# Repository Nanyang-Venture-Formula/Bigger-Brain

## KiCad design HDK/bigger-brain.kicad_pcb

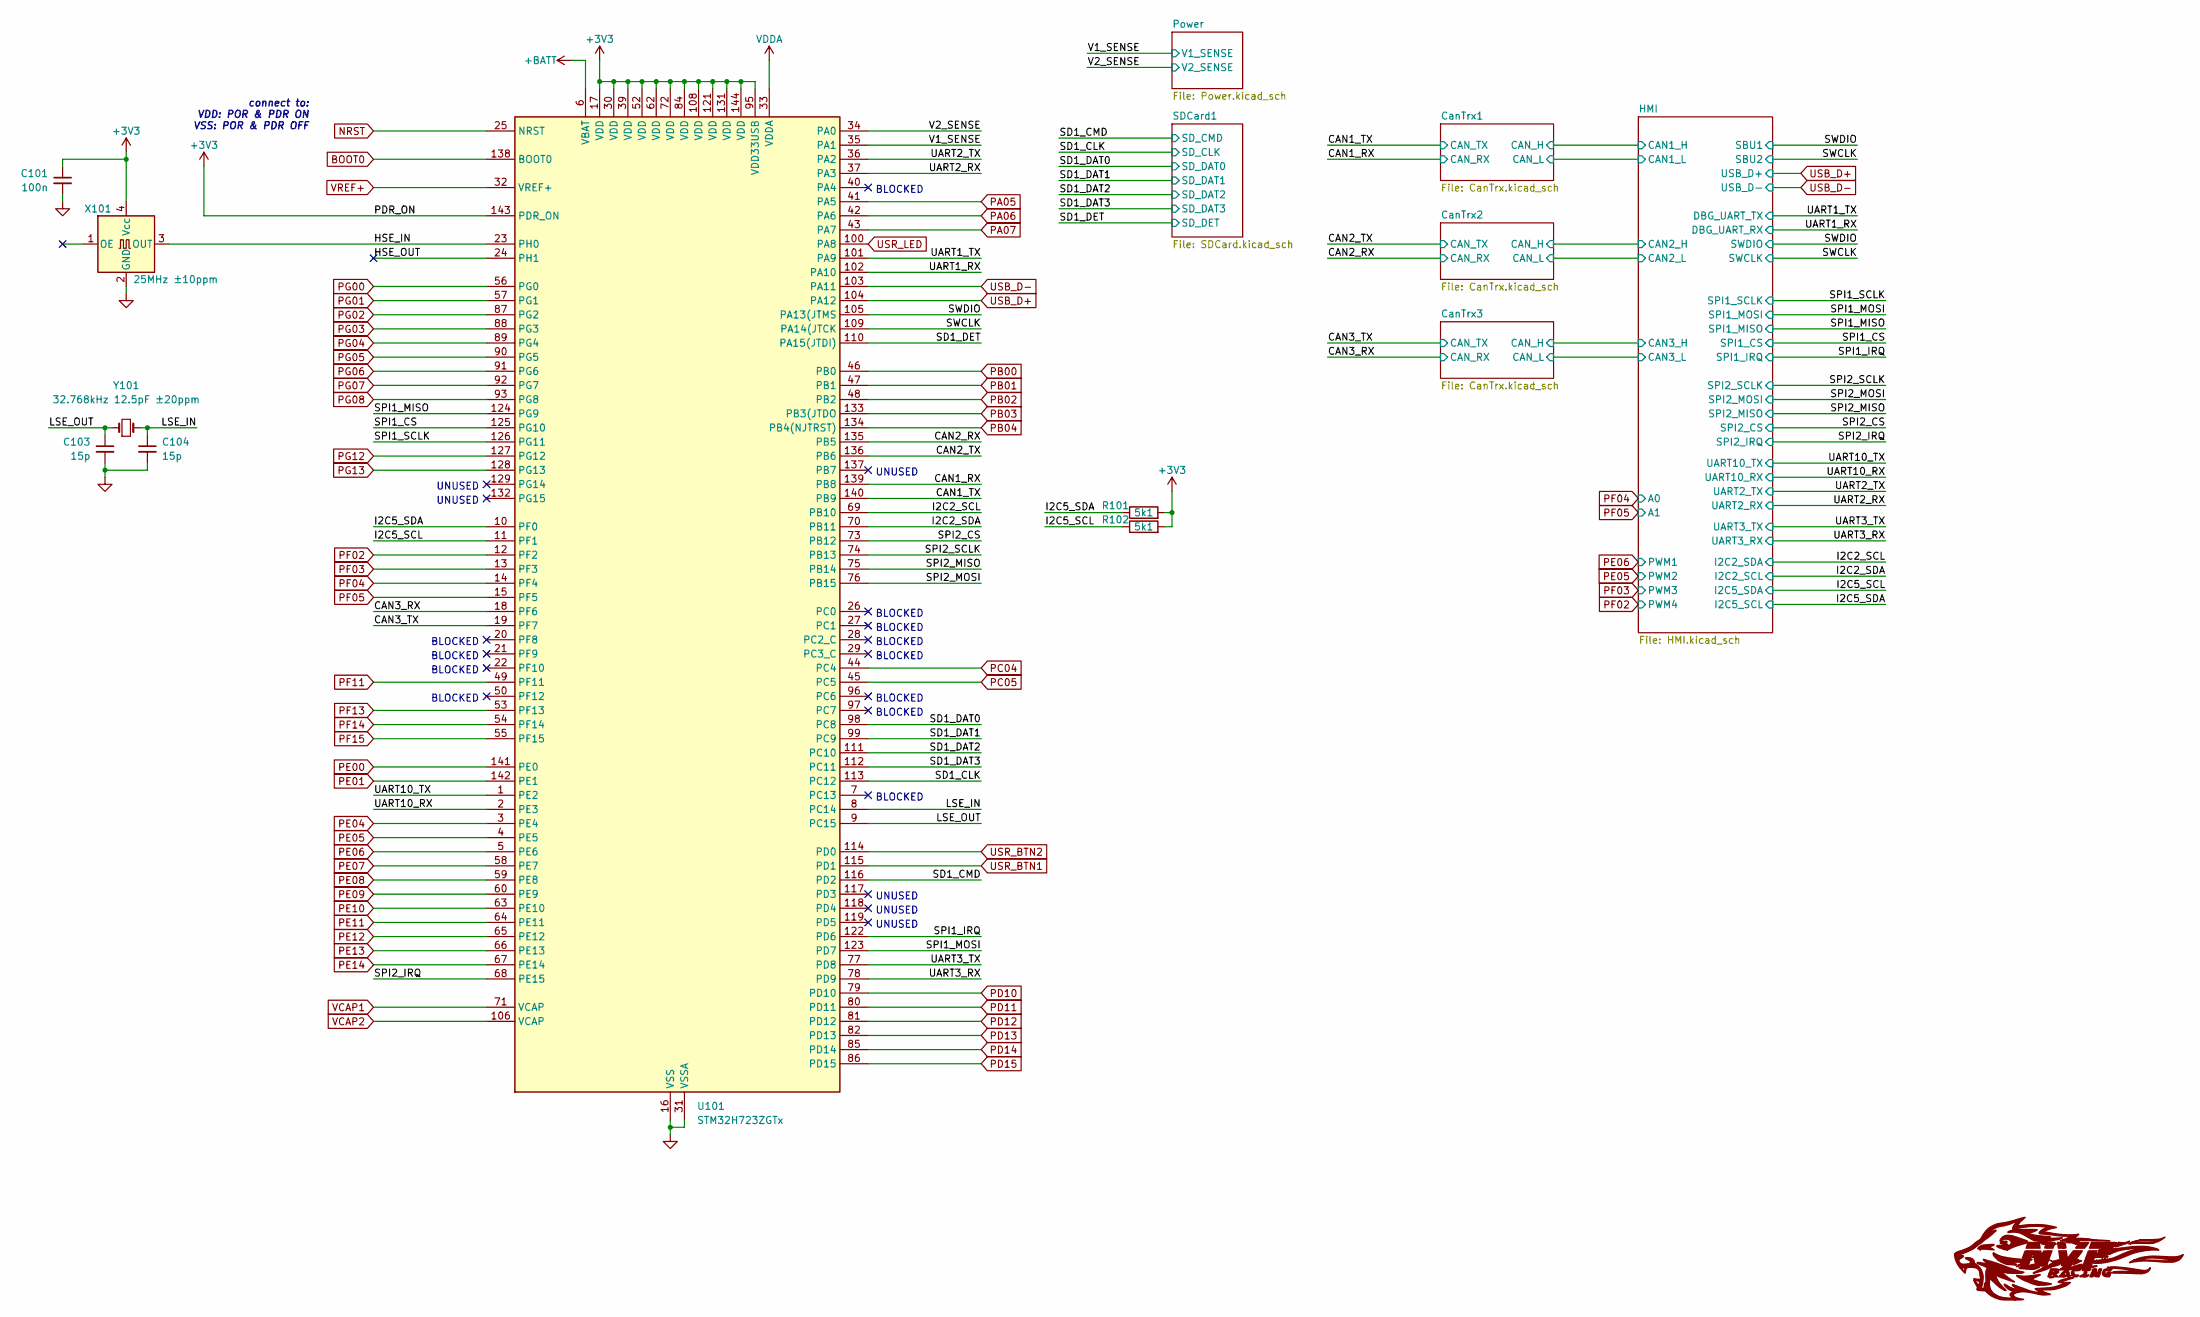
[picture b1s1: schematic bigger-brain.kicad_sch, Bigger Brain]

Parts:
C101: 100n; C_0603_1608Metric; LCSC C14663
C103, C104: 15p; C_0603_1608Metric; LCSC C1644
R101, R102: 5k1; R_0603_1608Metric; LCSC C23186
U101: STM32H723ZGTx; LQFP-144_20x20mm_P0.5mm; LCSC C730146
X101: 25MHz ±10ppm; Crystal_SMD_3225-4Pin_3.2x2.5mm; LCSC C669088
Y101: 32.768kHz 12.5pF ±20ppm; Crystal_SMD_3215-2Pin_3.2x1.5mm; LCSC C32346

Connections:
+BATT: U101.6 (VBAT); also elsewhere on the board
/CAN1_RX: U101.139 (PB8); also elsewhere on the board
/CAN1_TX: U101.140 (PB9); also elsewhere on the board
/CAN2_RX: U101.135 (PB5); also elsewhere on the board
/CAN2_TX: U101.136 (PB6); also elsewhere on the board
/CAN3_RX: U101.18 (PF6); also elsewhere on the board
/CAN3_TX: U101.19 (PF7); also elsewhere on the board
/HSE_IN: U101.23 (PH0), X101.3 (OUT)
/HSE_OUT: U101.24 (PH1)
/I2C2_SCL: U101.69 (PB10); also elsewhere on the board
/I2C2_SDA: U101.70 (PB11); also elsewhere on the board
/I2C5_SCL: R102.1, U101.11 (PF1); also elsewhere on the board
/I2C5_SDA: R101.1, U101.10 (PF0); also elsewhere on the board
/LSE_IN: C104.1, U101.8 (PC14), Y101.2
/LSE_OUT: C103.1, U101.9 (PC15), Y101.1
/SD1_CLK: U101.113 (PC12); also elsewhere on the board
/SD1_CMD: U101.116 (PD2); also elsewhere on the board
/SD1_DAT0: U101.98 (PC8); also elsewhere on the board
/SD1_DAT1: U101.99 (PC9); also elsewhere on the board
/SD1_DAT2: U101.111 (PC10); also elsewhere on the board
/SD1_DAT3: U101.112 (PC11); also elsewhere on the board
/SD1_DET: U101.110 (PA15(JTDI)); also elsewhere on the board
/SPI1_CS: U101.125 (PG10); also elsewhere on the board
/SPI1_IRQ: U101.122 (PD6); also elsewhere on the board
/SPI1_MISO: U101.124 (PG9); also elsewhere on the board
/SPI1_MOSI: U101.123 (PD7); also elsewhere on the board
/SPI1_SCLK: U101.126 (PG11); also elsewhere on the board
/SPI2_CS: U101.73 (PB12); also elsewhere on the board
/SPI2_IRQ: U101.68 (PE15); also elsewhere on the board
/SPI2_MISO: U101.75 (PB14); also elsewhere on the board
/SPI2_MOSI: U101.76 (PB15); also elsewhere on the board
/SPI2_SCLK: U101.74 (PB13); also elsewhere on the board
/SWCLK: U101.109 (PA14(JTCK); also elsewhere on the board
/SWDIO: U101.105 (PA13(JTMS); also elsewhere on the board
/UART1_RX: U101.102 (PA10); also elsewhere on the board
/UART1_TX: U101.101 (PA9); also elsewhere on the board
/UART2_RX: U101.37 (PA3); also elsewhere on the board
/UART2_TX: U101.36 (PA2); also elsewhere on the board
/UART3_RX: U101.78 (PD9); also elsewhere on the board
/UART3_TX: U101.77 (PD8); also elsewhere on the board
/UART10_RX: U101.2 (PE3); also elsewhere on the board
/UART10_TX: U101.1 (PE2); also elsewhere on the board
/V1_SENSE: U101.35 (PA1); also elsewhere on the board
/V2_SENSE: U101.34 (PA0); also elsewhere on the board
BOOT0: U101.138 (BOOT0); also elsewhere on the board
GND: C101.2, C103.2, C104.2, U101.16 (VSS), U101.31 (VSSA), U101.38 (VSS), U101.51 (VSS), U101.61 (VSS), U101.83 (VSS), U101.94 (VSS), U101.107 (VSS), U101.120 (VSS), U101.130 (VSS), X101.2 (GND); also elsewhere on the board
MCU-3.3V: C101.1, R101.2, R102.2, U101.17 (VDD), U101.30 (VDD), U101.39 (VDD), U101.52 (VDD), U101.62 (VDD), U101.72 (VDD), U101.84 (VDD), U101.95 (VDD33USB), U101.108 (VDD), U101.121 (VDD), U101.131 (VDD), U101.143 (PDR_ON), U101.144 (VDD), X101.4 (Vcc); also elsewhere on the board
NRST: U101.25 (NRST); also elsewhere on the board
PA05: U101.41 (PA5); also elsewhere on the board
PA06: U101.42 (PA6); also elsewhere on the board
PA07: U101.43 (PA7); also elsewhere on the board
PB00: U101.46 (PB0); also elsewhere on the board
PB01: U101.47 (PB1); also elsewhere on the board
PB02: U101.48 (PB2); also elsewhere on the board
PB03: U101.133 (PB3(JTDO); also elsewhere on the board
PB04: U101.134 (PB4(NJTRST)); also elsewhere on the board
PC04: U101.44 (PC4); also elsewhere on the board
PC05: U101.45 (PC5); also elsewhere on the board
PD10: U101.79 (PD10); also elsewhere on the board
PD11: U101.80 (PD11); also elsewhere on the board
PD12: U101.81 (PD12); also elsewhere on the board
PD13: U101.82 (PD13); also elsewhere on the board
PD14: U101.85 (PD14); also elsewhere on the board
PD15: U101.86 (PD15); also elsewhere on the board
PE00: U101.141 (PE0); also elsewhere on the board
PE01: U101.142 (PE1); also elsewhere on the board
PE04: U101.3 (PE4)
PE05: U101.4 (PE5); also elsewhere on the board
PE06: U101.5 (PE6); also elsewhere on the board
PE07: U101.58 (PE7); also elsewhere on the board
PE08: U101.59 (PE8); also elsewhere on the board
PE09: U101.60 (PE9); also elsewhere on the board
PE10: U101.63 (PE10); also elsewhere on the board
PE11: U101.64 (PE11); also elsewhere on the board
PE12: U101.65 (PE12); also elsewhere on the board
PE13: U101.66 (PE13); also elsewhere on the board
PE14: U101.67 (PE14); also elsewhere on the board
PF02: U101.12 (PF2); also elsewhere on the board
PF03: U101.13 (PF3); also elsewhere on the board
PF04: U101.14 (PF4); also elsewhere on the board
PF05: U101.15 (PF5); also elsewhere on the board
PF11: U101.49 (PF11); also elsewhere on the board
PF13: U101.53 (PF13); also elsewhere on the board
PF14: U101.54 (PF14); also elsewhere on the board
PF15: U101.55 (PF15); also elsewhere on the board
PG00: U101.56 (PG0); also elsewhere on the board
PG01: U101.57 (PG1); also elsewhere on the board
PG02: U101.87 (PG2); also elsewhere on the board
PG03: U101.88 (PG3); also elsewhere on the board
PG04: U101.89 (PG4); also elsewhere on the board
PG05: U101.90 (PG5); also elsewhere on the board
PG06: U101.91 (PG6); also elsewhere on the board
PG07: U101.92 (PG7); also elsewhere on the board
PG08: U101.93 (PG8); also elsewhere on the board
PG12: U101.127 (PG12); also elsewhere on the board
PG13: U101.128 (PG13); also elsewhere on the board
USB_D+: U101.104 (PA12); also elsewhere on the board
USB_D-: U101.103 (PA11); also elsewhere on the board
USR_BTN1: U101.115 (PD1); also elsewhere on the board
USR_BTN2: U101.114 (PD0); also elsewhere on the board
USR_LED: U101.100 (PA8); also elsewhere on the board
VCAP1: U101.71 (VCAP); also elsewhere on the board
VCAP2: U101.106 (VCAP); also elsewhere on the board
VDDA: U101.33 (VDDA); also elsewhere on the board
VREF+: U101.32 (VREF+); also elsewhere on the board

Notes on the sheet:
UNUSED
BLOCKED
connect to: VDD: POR & PDR ON VSS: POR & PDR OFF

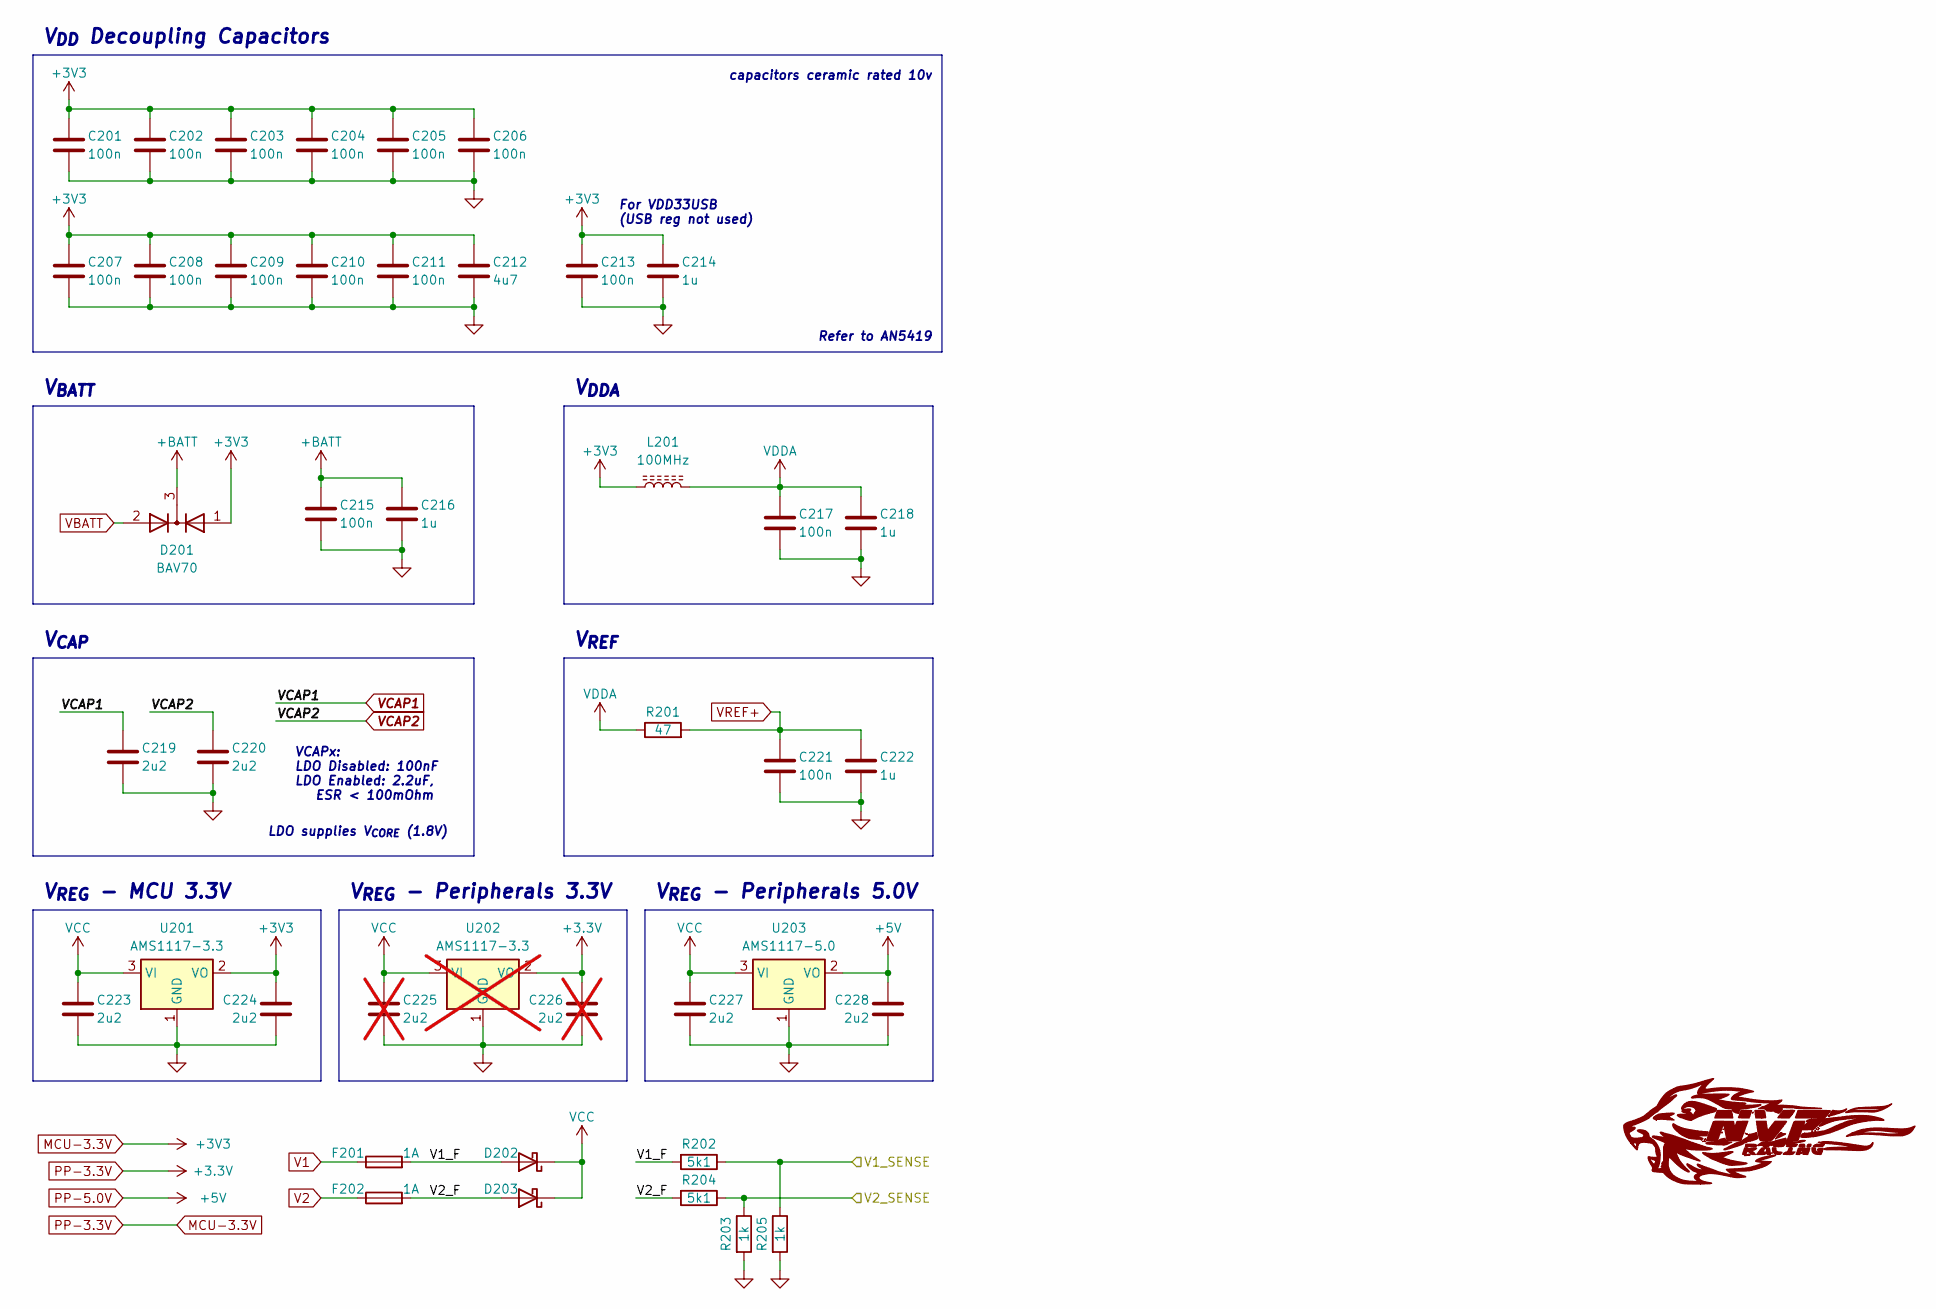
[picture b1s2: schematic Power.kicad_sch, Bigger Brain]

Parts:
C201, C202, C203, C204, C205, C206, C207, C208, C209, C210, C211, C213, C215, C217, C221: 100n; C_0603_1608Metric; LCSC C14663
C212: 4u7; C_0805_2012Metric; LCSC C1779
C214, C216, C218, C222: 1u; C_0805_2012Metric; LCSC C28323
C219, C220, C223, C224, C227, C228: 2u2; C_0805_2012Metric; LCSC C377773
C225, C226: 2u2; C_0805_2012Metric; LCSC C377773; not fitted
D201: BAV70; SOT-23; LCSC C68978
D202, D203: SS14; D_SMA; LCSC C2480
F201, F202: 1A; FUSE-Littelfuse_Nano2_154x; LCSC C206910
L201: 100MHz; R_0805_2012Metric; LCSC C1015
R201: 47; R_0603_1608Metric; LCSC C23182
R202, R204: 5k1; R_0603_1608Metric; LCSC C23186
R203, R205: 1k; R_0603_1608Metric; LCSC C21190
U201: AMS1117-3.3; SOT-223-3_TabPin2; LCSC C6186
U202: AMS1117-3.3; SOT-223-3_TabPin2; LCSC C6186; not fitted
U203: AMS1117-5.0; SOT-223-3_TabPin2; LCSC C6187

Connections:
+BATT: C215.1, C216.1, D201.3 (K); also elsewhere on the board
/Power/V1_F: D202.2 (A), F201.2, R202.2
/Power/V2_F: D203.2 (A), F202.2, R204.2
/V1_SENSE: R202.1, R205.1; also elsewhere on the board
/V2_SENSE: R203.1, R204.1; also elsewhere on the board
GND: C201.2, C202.2, C203.2, C204.2, C205.2, C206.2, C207.2, C208.2, C209.2, C210.2, C211.2, C212.2, C213.2, C214.2, C215.2, C216.2, C217.2, C218.2, C219.2, C220.2, C221.2, C222.2, C223.2, C224.2, C225.2, C226.2, C227.2, C228.2, R203.2, R205.2, U201.1 (GND), U202.1 (GND), U203.1 (GND); also elsewhere on the board
MCU-3.3V: C201.1, C202.1, C203.1, C204.1, C205.1, C206.1, C207.1, C208.1, C209.1, C210.1, C211.1, C212.1, C213.1, C214.1, C224.1, C226.1, D201.1 (A), L201.1, U201.2 (VO), U202.2 (VO); also elsewhere on the board
PP-5.0V: C228.1, U203.2 (VO); also elsewhere on the board
V1: F201.1; also elsewhere on the board
V2: F202.1; also elsewhere on the board
VBATT: D201.2 (A); also elsewhere on the board
VCAP1: C219.1; also elsewhere on the board
VCAP2: C220.1; also elsewhere on the board
VCC: C223.1, C225.1, C227.1, D202.1 (K), D203.1 (K), U201.3 (VI), U202.3 (VI), U203.3 (VI); also elsewhere on the board
VDDA: C217.1, C218.1, L201.2, R201.1; also elsewhere on the board
VREF+: C221.1, C222.1, R201.2; also elsewhere on the board

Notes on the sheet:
V_{REF}
V_{REG} - Peripherals 3.3V
capacitors ceramic rated 10v
V_{CAP}
LDO supplies V_{CORE} (1.8V)
For VDD33USB (USB reg not used)
VCAPx: LDO Disabled: 100nF LDO Enabled: 2.2uF, ESR < 100mOhm
V_{REG} - Peripherals 5.0V
V_{DDA}
V_{DD} Decoupling Capacitors
Refer to AN5419
V_{REG} - MCU 3.3V
V_{BATT}

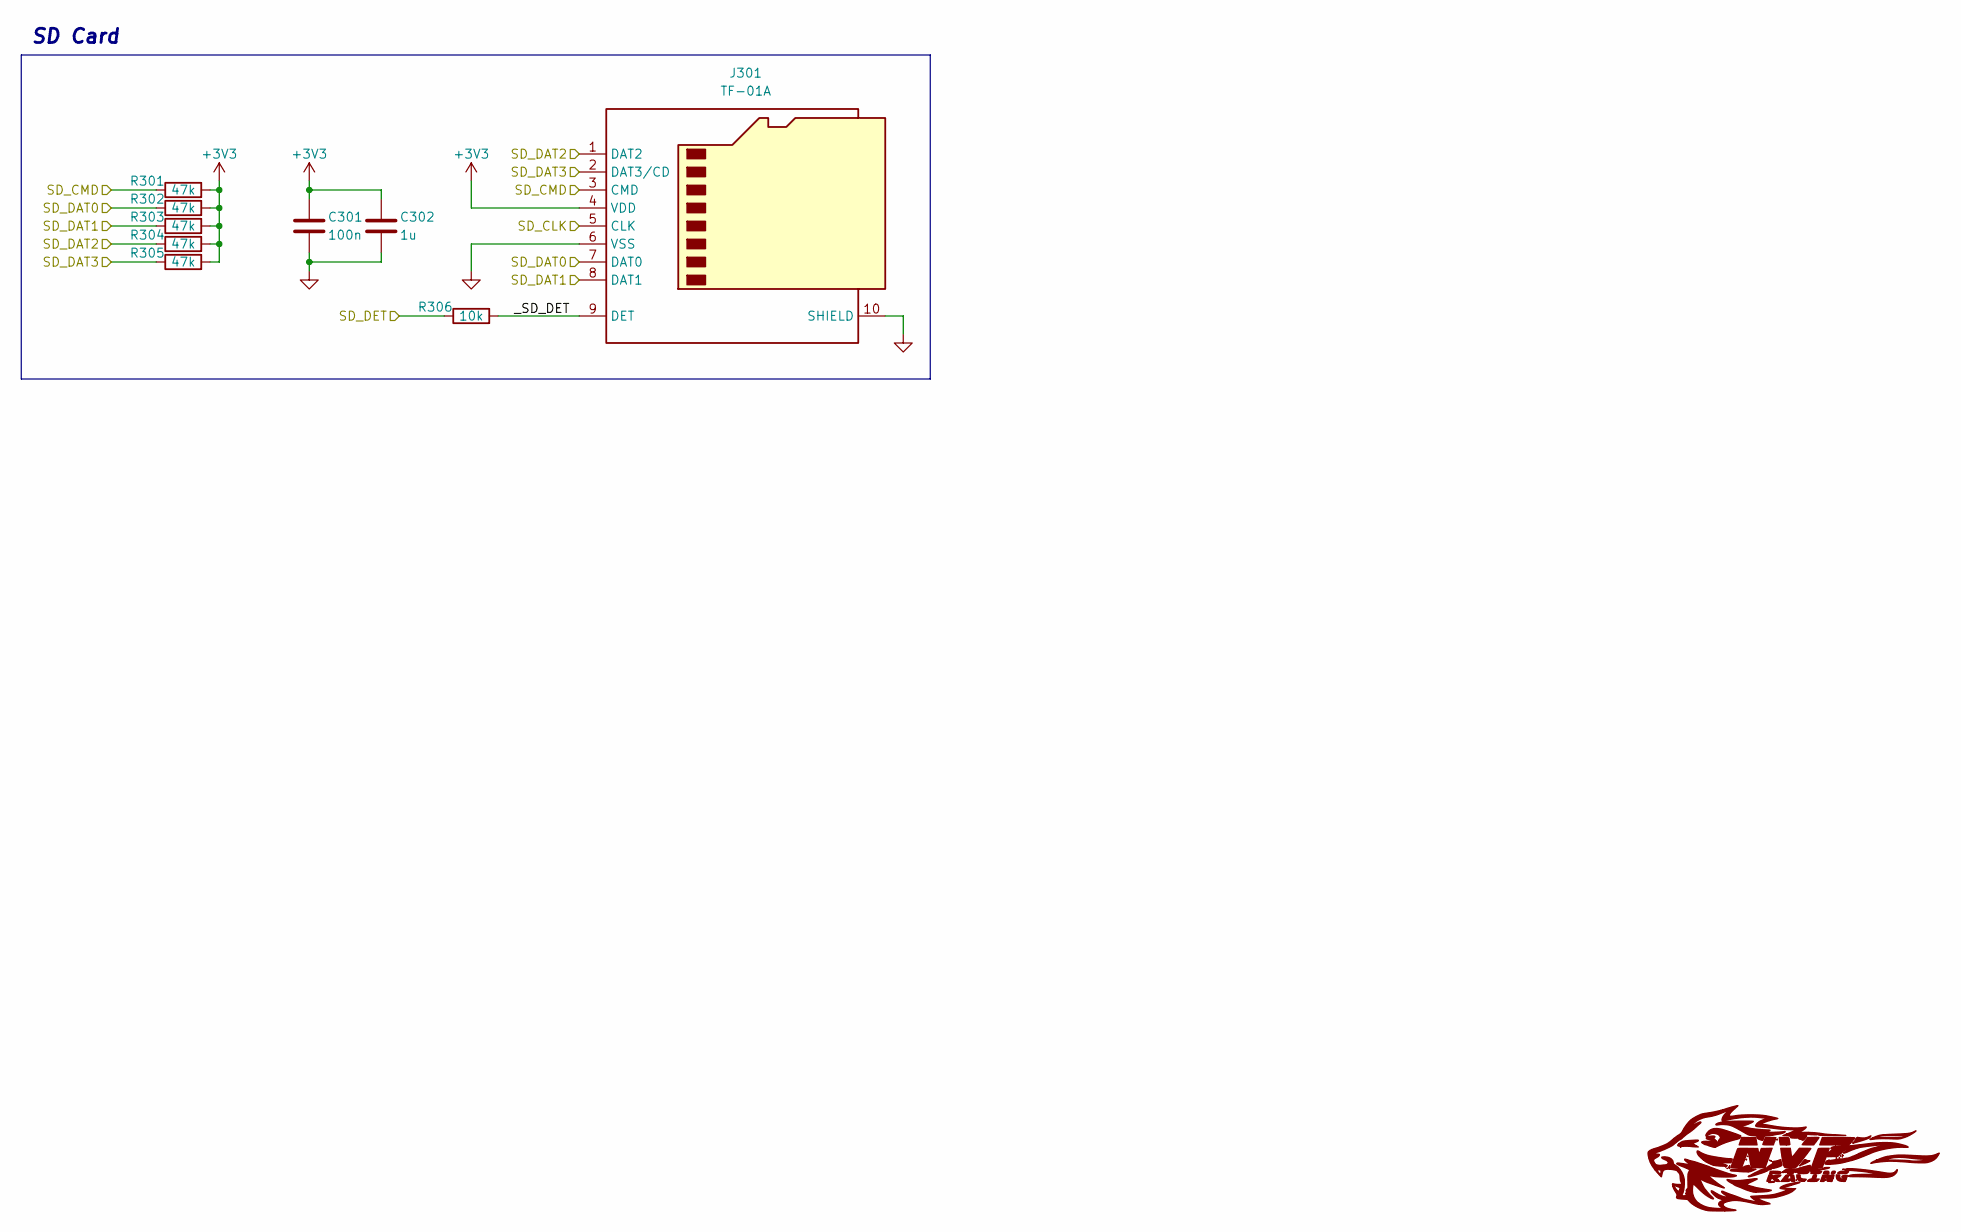
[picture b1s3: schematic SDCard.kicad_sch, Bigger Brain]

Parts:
C301: 100n; C_0603_1608Metric; LCSC C14663
C302: 1u; C_0805_2012Metric; LCSC C28323
J301: TF-01A; TFCard_TF-01A; LCSC C91145
R301, R302, R303, R304, R305: 47k; R_0603_1608Metric; LCSC C25819
R306: 10k; R_0603_1608Metric; LCSC C25804

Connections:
/SD1_CLK: J301.5 (CLK); also elsewhere on the board
/SD1_CMD: J301.3 (CMD), R301.1; also elsewhere on the board
/SD1_DAT0: J301.7 (DAT0), R302.1; also elsewhere on the board
/SD1_DAT1: J301.8 (DAT1), R303.1; also elsewhere on the board
/SD1_DAT2: J301.1 (DAT2), R304.1; also elsewhere on the board
/SD1_DAT3: J301.2 (DAT3/CD), R305.1; also elsewhere on the board
/SD1_DET: R306.1; also elsewhere on the board
/SDCard1/_SD_DET: J301.9 (DET), R306.2
GND: C301.2, C302.2, J301.6 (VSS), J301.10 (SHIELD); also elsewhere on the board
MCU-3.3V: C301.1, C302.1, J301.4 (VDD), R301.2, R302.2, R303.2, R304.2, R305.2; also elsewhere on the board

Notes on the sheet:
SD Card

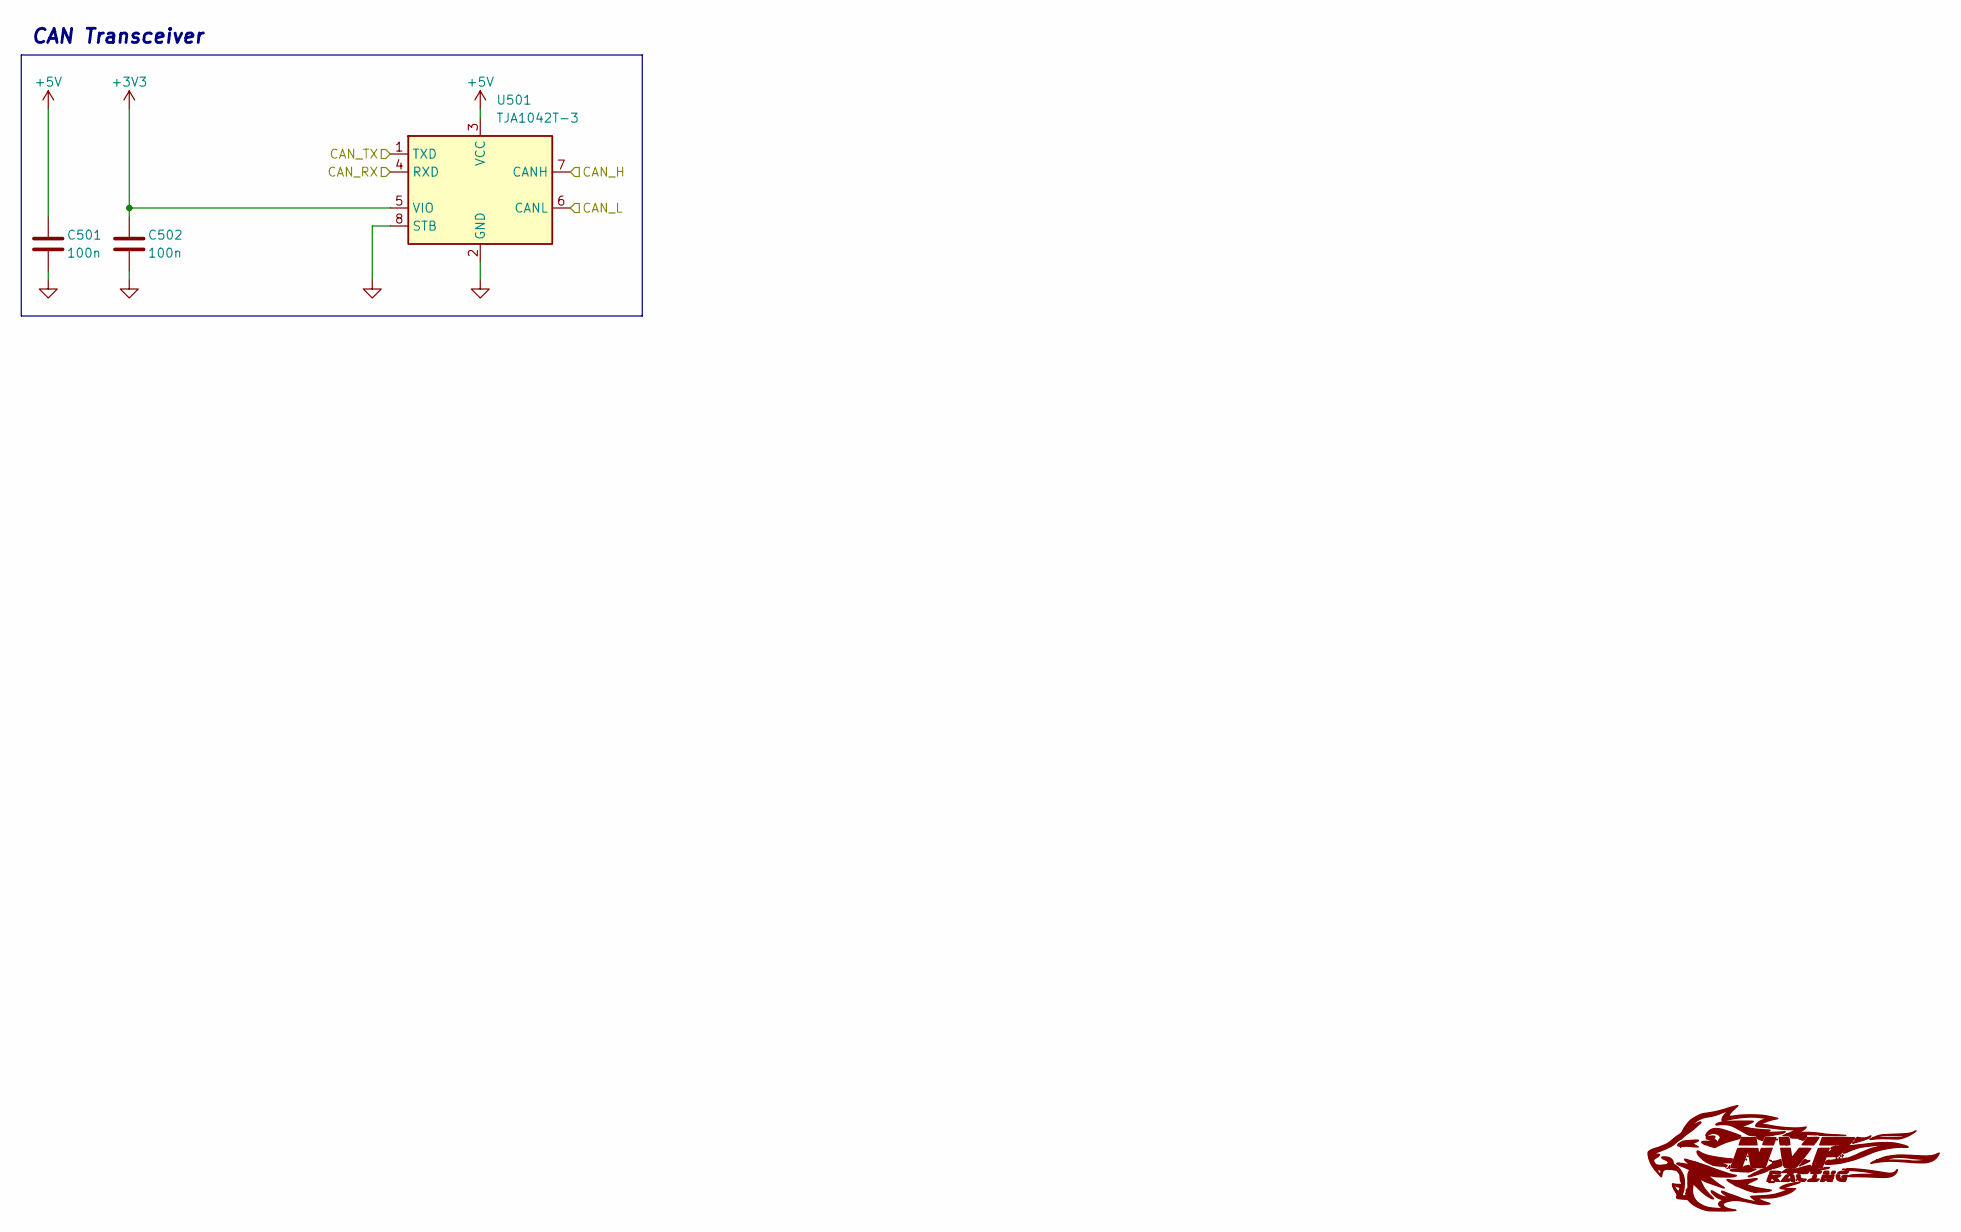
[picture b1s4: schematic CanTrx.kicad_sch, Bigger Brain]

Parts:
C501, C502: 100n; C_0603_1608Metric; LCSC C14663
U501: TJA1042T-3; SOIC-8_3.9x4.9mm_P1.27mm; LCSC C132227

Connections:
/CAN1_RX: U501.4 (RXD); also elsewhere on the board
/CAN1_TX: U501.1 (TXD); also elsewhere on the board
/CanTrx1/CAN_H: U501.7 (CANH); also elsewhere on the board
/CanTrx1/CAN_L: U501.6 (CANL); also elsewhere on the board
GND: C501.2, C502.2, U501.2 (GND), U501.8 (STB); also elsewhere on the board
MCU-3.3V: C502.1, U501.5 (VIO); also elsewhere on the board
PP-5.0V: C501.1, U501.3 (VCC); also elsewhere on the board

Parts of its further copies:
C601, C602, C701, C702: 100n; C_0603_1608Metric; LCSC C14663
U601, U701: TJA1042T-3; SOIC-8_3.9x4.9mm_P1.27mm; LCSC C132227

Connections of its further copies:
/CAN2_RX: U601.4 (RXD); also elsewhere on the board
/CAN2_TX: U601.1 (TXD); also elsewhere on the board
/CAN3_RX: U701.4 (RXD); also elsewhere on the board
/CAN3_TX: U701.1 (TXD); also elsewhere on the board
/CanTrx2/CAN_H: U601.7 (CANH); also elsewhere on the board
/CanTrx2/CAN_L: U601.6 (CANL); also elsewhere on the board
/CanTrx3/CAN_H: U701.7 (CANH); also elsewhere on the board
/CanTrx3/CAN_L: U701.6 (CANL); also elsewhere on the board
GND: C601.2, C602.2, C701.2, C702.2, U601.2 (GND), U601.8 (STB), U701.2 (GND), U701.8 (STB); also elsewhere on the board
MCU-3.3V: C602.1, C702.1, U601.5 (VIO), U701.5 (VIO); also elsewhere on the board
PP-5.0V: C601.1, C701.1, U601.3 (VCC), U701.3 (VCC); also elsewhere on the board

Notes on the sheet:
CAN Transceiver
